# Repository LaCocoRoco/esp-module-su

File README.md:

# Sensor Unit

Sensor unit for measuring rain intensity and wind speed.

## Guidline

1. Order PCB by uploading the [Gerber File](pcb/cam/esp-module-su.zip) to [JLCPCB](https://jlcpcb.com/).
2. Order Parts by uploading the [BOM File](pcb/bom/esp-module-su.csv) to [LCSC](https://www.lcsc.com/bom).
3. Build PCB by placing components as visualized in the [BOM Viewer](https://htmlpreview.github.io/?https://github.com/LaCocoRoco/esp-module-su/blob/main/pcb/bom/esp-module-su.html).
4. Download & Install [Git](https://git-scm.com/), [CP210x Driver](https://www.silabs.com/developers/usb-to-uart-bridge-vcp-drivers?tab=downloads) and [VSCode](https://code.visualstudio.com/) with [PlatformIO](https://platformio.org/) Extension.
5. Clone the Repository `git clone --recursive https://github.com/LaCocoRoco/esp-module-su.git`.
6. With PlatformIO `Upload Filsystem Image` & `Upload & Monitor ` to your board.

## Module Modes

Modes can be changed by pressing the mode button.  
An audio signal will provide feedback for the active mode.  
Holding the mode button for more than two seconds will clear the module.

### Low Power Mode

- Feedback with one audio signal
- All web functionality is disabled
- Device will enter deep sleep when inactive
- Battery lifetime of several months

### Hybrid Mode

- Feedback with two audio signals
- All web functionality is disabled
- Device will enter deep sleep when battery voltage is below 3.8V
- Battery lifetime of several days

### Web Mode

- Feedback with three audio signals
- All web functionality is enabled
- Battery lifetime of several hours

## Importend

All modules have three different modes: Web Mode, Hybrid Mode, and Low Power Mode.  
The Wi-Fi can be configured as either Access Point or Station Mode.  
However, due to the use of the EspNow protocol for communication, there are some restrictions.

### Modules Set Up as Access Points (Default):

- All modes work without any restrictions.

### Modules Set Up in Station Mode:

- Web Mode works without any restrictions.
- Low Power Mode and Hybrid Mode only work if the Wi-Fi network is set to a **fixed channel**.

### Modules Set Up in Access Point or Station Mode:

- All modes only work if the Wi-Fi network is set to **channel 1**.

## Explanation

The main goal of this project was to avoid reliance on any infrastructure. For configuration, neither an application nor an existing Wi-Fi network is necessary. All modules can be accessed via the corresponding SSID in Access Point Mode or via hostname in Station Mode. However, there are some trade-offs:

To reduce power consumption in Low Power Mode, the module does not establish a direct network connection. It only broadcasts data to the specified receiver. In Station Mode, the network may change the Wi-Fi channel occasionally. Connecting to the network to receive this information would significantly increase uptime.

An alternative approach to this problem would be to scan for the receiver and request the channel. However, this has additional drawbacks:

- Scanning for this information takes some time (though less compared to connecting to a Wi-Fi network).
- It is difficult to distinguish whether a transmission failure is due to the wrong channel or a general network issue.
- Continuously requesting this information until a response is received would quickly add to the uptime and increase power consumption.

This is the reason why the relevant points must be considered mentioned in the [Importand](#importend) section.

## Reference

- [VSCode](https://code.visualstudio.com/) - Lightweight code editor.
- [PlatformIO](https://platformio.org/) - Embedded software development gateway.
- [Autodesk Fusion 360](https://www.autodesk.com/products/fusion-360) - Design and manufacturing software for CAD, CAM, CAE, and PCB.
- [Autodesk Eagle](https://www.autodesk.com/products/eagle) - Electronic design automation software for printed circuit boards.
- [JLCPCB](https://jlcpcb.com/) - Reasonably priced PCB manufacturer.
- [LCSC](https://www.lcsc.com/) - Supplier for a wide selection of electronic components.
- [CP210x Driver](https://www.silabs.com/developers/usb-to-uart-bridge-vcp-drivers?tab=downloads) - USB to UART Driver for uploading codebase.
- [InteractiveHtmlBom](https://github.com/openscopeproject/InteractiveHtmlBom) - Bill of materials listing to visually search for components and their placements.

## Preview

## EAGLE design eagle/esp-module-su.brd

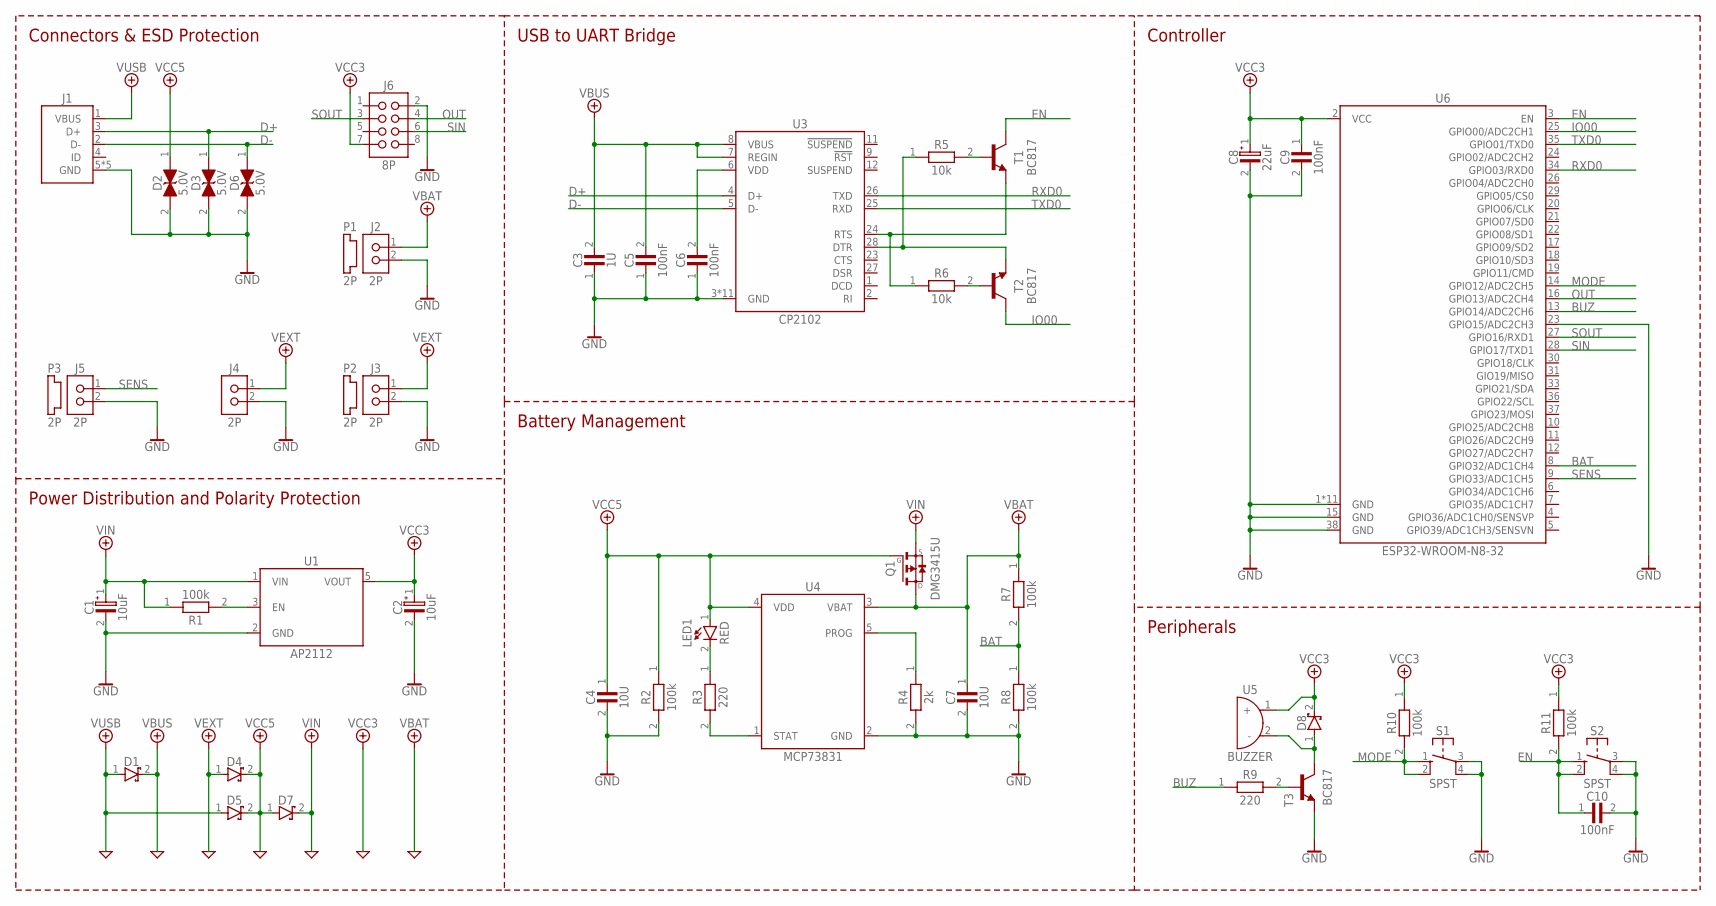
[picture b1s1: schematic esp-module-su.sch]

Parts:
C1, C2: 10uF; I1206-M3216-D
C3: 1U; I0805-M2012-C
C4, C7: 10U; I0805-M2012-C
C5, C6, C9, C10: 100nF; I0805-M2012-C
C8: 22uF; I1206-M3216-D
D1, D4, D5, D7, D8: 30V; SOD-323
D2, D3, D6: 5.0V; SOD-523
J1: USB-A-MICRO-SMD-SIDE
J2, J3, J5: 2P; JST-S2B-PH-SM4-TB
J4: 2P; PZ254V-11-02P
J6: 8P; PM254V-12-08-H85
LED1: RED; I0805-M2012-D
P1, P2, P3: 2P; CONNECTOR-DEFAULT
Q1: DMG3415U; SOT-23-3
R1, R2, R7, R8, R10, R11: 100k; I0805-M2012-R
R3, R9: 220; I0805-M2012-R
R4: 2k; I0805-M2012-R
R5, R6: 10k; I0805-M2012-R
S1, S2: SPST; SMD-SW-4
T1, T2, T3: BC817; SOT-23-3
U1: AP2112; SOT-25-5
U3: CP2102; QFN-28
U4: MCP73831; SOT-23-5
U5: BUZZER; SMD-BUZZER
U6: ESP32-WROOM-N8-32; ESP32-WROOM-32

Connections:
ABEN: R1.2, U1.3 (EN)
BAT: R7.2, R8.1, U6.8 (GPIO32/ADC1CH4)
BUZ: R9.1, U6.13 (GPIO14/ADC2CH6)
BZB: R9.2, T3.1 (B)
BZC: D8.1 (A), T3.3 (C), U5.2 (-)
D+: D3.1 (A), J1.3 (D+), U3.4 (D+)
D-: D6.1 (A), J1.2 (D-), U3.5 (D-)
DTR1: R5.1, T2.2 (E), U3.28 (DTR)
DTRT1: R5.2, T1.1 (B)
EN: C10.1, R11.2, S2.1, S2.2, T1.3 (C), U6.3 (EN)
GND: C1.2 (-), C2.2 (-), C3.1, C4.2, C5.1, C6.1, C7.2, C8.2 (-), C9.2, C10.2, D2.2 (C), D3.2 (C), D6.2 (C), J1.5 (GND), J1.6 (GND), J1.7 (GND), J1.8 (GND), J1.9 (GND), J2.2, J3.2, J4.2, J5.2, J6.2, R2.2, R4.2, R8.2, S1.3, S1.4, S2.3, S2.4, T3.2 (E), U1.2 (GND), U3.3 (GND), U3.29 (GND), U3.30 (GND), U3.31 (GND), U3.32 (GND), U3.33 (GND), U3.34 (GND), U3.35 (GND), U3.36 (GND), U3.37 (GND), U3.38 (GND), U4.2 (GND), U6.1 (GND), U6.15 (GND), U6.23 (GPIO15/ADC2CH3), U6.38 (GND), U6.39 (GND), U6.40 (GND), U6.41 (GND), U6.42 (GND), U6.43 (GND), U6.44 (GND), U6.45 (GND), U6.46 (GND), U6.47 (GND), U6.48 (GND)
IO00: T2.3 (C), U6.25 (GPIO00/ADC2CH1)
MODE: R10.2, S1.1, S1.2, U6.14 (GPIO12/ADC2CH5)
OUT: J6.4, U6.16 (GPIO13/ADC2CH4)
PROG1: R4.1, U4.5 (PROG)
RTS1: R6.1, T1.2 (E), U3.24 (RTS)
RTST1: R6.2, T2.1 (B)
RXD0: U3.26 (TXD), U6.34 (GPIO03/RXD0)
SENS: J5.1, U6.9 (GPIO33/ADC1CH5)
SIN: J6.6, U6.28 (GPIO17/TXD1)
SOUT: J6.3, U6.27 (GPIO16/RXD1)
STAT1: R3.2, U4.1 (STAT)
STATLED1: LED1.2 (C), R3.1
TXD0: U3.25 (RXD), U6.35 (GPIO01/TXD0)
VBAT: C7.1, J2.1, Q1.3 (D), R7.1, U4.3 (VBAT)
VBUS: C3.2, C5.2, D1.2 (C), U3.7 (REGIN), U3.8 (VBUS)
VCC3: C2.1 (+), C8.1 (+), C9.1, D8.2 (C), J6.7, R10.1, R11.1, U1.5 (VOUT), U5.1 (+), U6.2 (VCC)
VCC5: C4.1, D2.1 (A), D4.2 (C), D5.2 (C), D7.1 (A), LED1.1 (A), Q1.1 (G), R2.1, U4.4 (VDD)
VDD: C6.2, U3.6 (VDD)
VEXT: D4.1 (A), J3.1, J4.1
VIN: C1.1 (+), D7.2 (C), Q1.2 (S), R1.1, U1.1 (VIN)
VUSB: D1.1 (A), D5.1 (A), J1.1 (VBUS)

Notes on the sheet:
USB to UART Bridge
Connectors & ESD Protection
Battery Management
Power Distribution and Polarity Protection
Controller
Peripherals

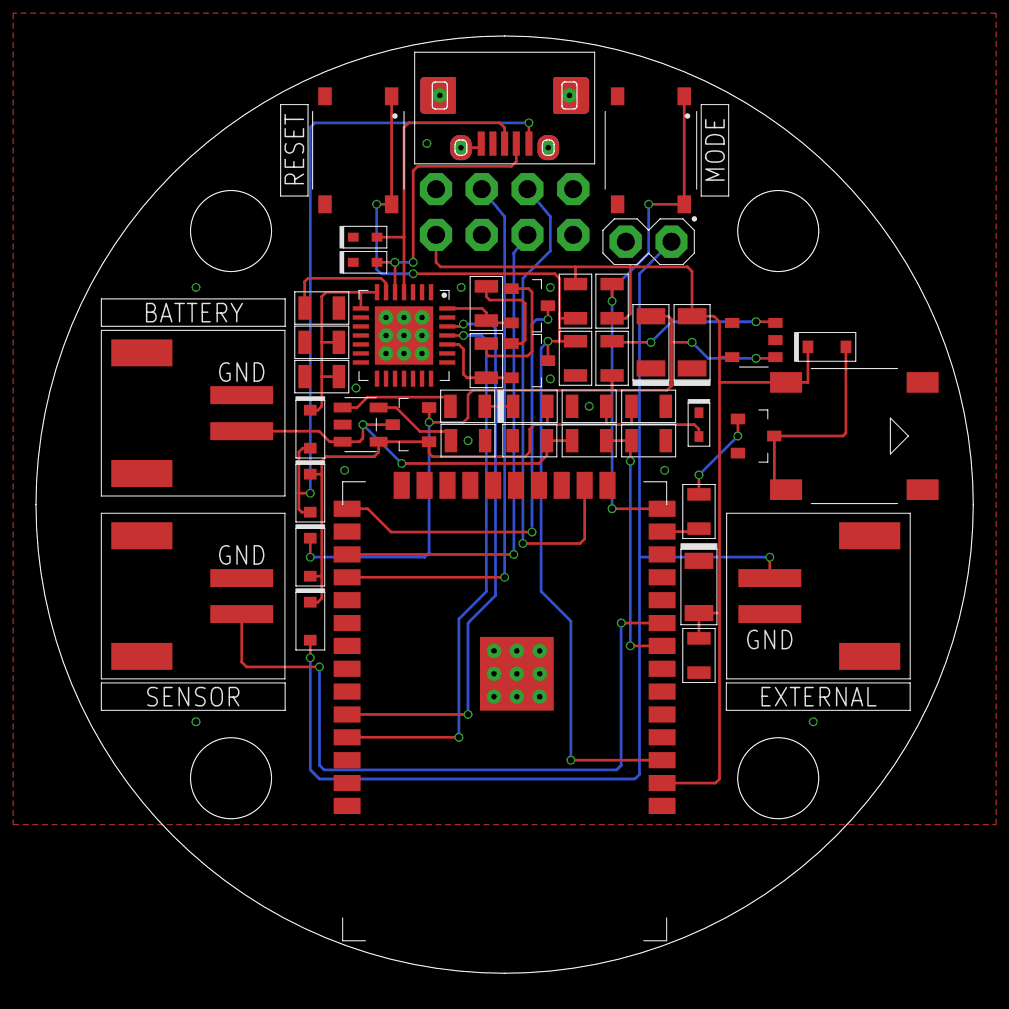
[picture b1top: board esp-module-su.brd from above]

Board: 2 copper layers, 52.1 x 52.1 mm, 50 parts (1 on the bottom side), 32 nets.
